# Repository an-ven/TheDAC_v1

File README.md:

# The DAC -The Digital Analog Clock

The primary goal of this project was to design and build a clock, without a single line of code running on the clock hardware. To do this, the time keeping circuit (the digital part) was implemented by hard-wiring together classic 74-series logic chips. The time display was implemented using three analog meters driven by three adjustable current sources (the analog part) controlled by the timekeeping circuit.

As an additional constraint, the circuit was built using only trough hole components (a welcome change of pace, since lately I mostly make circuits with surface mount components)

# Theory of operation

In general the circuit can be presented as follows (for full circuit schematic, refer to [circuit documentation](Documentation/TheDAC_v1.pdf)):

## Crystal oscillator and clock divider

Every clock needs a stable frequency source. In this case, it is based around a common 32,768kHz watch crystal (Y1) and the oscillator section of the 74HC4060 integrated circuit (U3). The chosen oscillator frequency is a power of two (`2^15 = 32768`) which can conveniently be divided down to 1Hz using binary counters.

The oscillator output of 74HC4060 is then internally connected to the first stage clock input of its 14-stage binary ripple counter section. Each counter stage is basically a T-type flip-flop that inverts (toggles) its output state when a falling edge is detected on its clock input. Effectively each stage divides its clock signal frequency by 2. Counter stages are wired in series, where each stage feeds the clock input of the next stage.

Given a 14 stage counter, its input clock frequency will be divided by `2^14 = 16384` on the output of its last (14th) stage. With the oscillator frequency 32,768kHz, the last counter stage will output a 2Hz signal which then gets sent to the seconds counter circuit. In this circuit, the 12th stage output (8Hz signal) is also used by the time setting user interface circuit. 

## Seconds, minutes and hours counters

Hours, minutes and seconds counters are each constructed around a 74HC4024 7-stage binary ripple counter

Looking at the seconds counter (U6), its clock input is driven by a 2Hz signal from the oscillator circuit, which gets divided to 1Hz by the counters first stage and output (Q0) to a test point and a LED (D4). Conveniently this 1Hz signal is also internally wired to the remaining 6 subsequent counter stages with their outputs (Q1 to Q6) representing the seconds count in parallel binary format.

When the seconds counter gets to 60 (or `111100` in binary), the counter should immediately (asynchronously) resets back to 0. This condition is detected by feeding the 4 most significant outputs (Q3 to Q6) in to one of 74HC21 4-input AND gates (U7B) which when all four inputs are high generates a high signal, which can then be used as a reset signal for the second counter and a clock pulse for the minutes counter.

The seconds counter reset signal gets combined with the user interface stop signal by a logic OR function implemented using two NOR gates (U5D and U5C). The clock pulse for the minutes counter is combined with the user interface increment seconds signal and inverted by a NOR gate (U5A).

Moving on to the minutes counter (U8), the circuit functions very similarly to the seconds counter circuit, with differences being that the first counter stage isn't needed for clock division and is directly used as the minutes count least significant bit (LSB) and the minutes counter reset signal is connected directly to the output of the 4-input AND gate (U7A). The last counter stage is simply ignored.

The hours counter follows much the same operating principles with the difference being, that it needs to reset when reaching 24 (`11000` in binary). This function is done by wiring the two most significant hour count bits (outputs Q3 and Q4) through a logical AND block (implemented using two NAND gates U4D and U4C) to the counter reset input. The last two counter stages are ignored.

Some basic logic functions such as hours reset logic AND circuit and seconds reset combining OR circuit have been implemented using multiple logic gates. This was done to avoid having to add additional logic chips with exact needed function and then have several unused logic gates in various chips (most classic 74-series basic logic gate chips usually have multiple logic gates per package)

## Digital to analog conversion and current driver circuit

As mentioned previously, seconds (6 bits), minutes (6 bits) and hours (5 bits) counters output their count values in parallel binary format. These outputs are used to drive 3 digital to analog converters (DAC) that are implemented as simple R-2R resistor ladders.

The analog voltage signals from R-2R DACs are then connected to the current driver inputs. A single current driver is implemented using one of four operational amplifier blocks of the LMC6484 Quad Op-Amp IC (U10). Each Op-Amp block amplifies the voltage difference between its two inputs: `V_out = G * (V(+) - V(-))`, where `G` is amplifier gain (usually a very large number). So if the `V(+)` input goes higher than `V(-)` the Op-Amp output `V_out` will also pull higher and vice versa.

The R-2R DAC output signal is fed in to the Op-Amp `V(+)` input, while its output is wired through an analog micro ampere meter in to its `V(-)` and then through a variable resistor to ground, forming a negative feedback loop. In this configuration the Op-Amp will drive its output so that the `V(-)` input voltage (voltage drop across the adjustable resistor) is effectively equal to `V(+)` input voltage.

With counters at their maximum values (59 for seconds and minutes counters and 23 for hours counter) the variable resistors are set so that the current needed to cause voltage drops across the adjustable resistor equal to ADC output voltage is equal full scale current of analog ampere meters. In this case very sensitive (50uA full range) analog ampere meters have been chosen, so that Op-Amp outputs are powerful enough to drive the needed full scale current without the need for any external amplification stages.  

The unused Op-Amp block has its inputs wired to its power supply rails, so that the output is forced in to a defined state. If the inputs were left floating, tit would be possible for the output to wander around unpredictably, possibly causing interference. In this application this probably wouldn't be an issue, but in a more sensitive circuit this could be critical.

## Time setting user interface

Time setting interface consists of three user inputs: a toggle switch that enables time setting mode and two push buttons used to manually increment minutes and hours counts. Closing the "run/stop" toggle switch (SW1) forces the seconds counter reset input high (stop signal), effectively stopping the counter and holding it at 0, wile also enabling minutes and hours setting push buttons (SW2 and SW3 respectively).

Push button contacts closing together isn't a perfect one time event due to contacts bouncing against each other before settling and completely closing together. The counter chips used in this circuit are more than fast enough to count individual contact bounce events which means one button press can be counted as wildly varying number of button presses. To filter contact bounce out from the push button signal a combination of a low-pass filter and schmitt trigger is used.

Looking at the minute setting circuit, SW2 push button signal (yellow trace) feeds in to the low pass filter consisting of resistor R5 and capacitor C7 (blue trace) which then feeds in to one of two inputs of a 74HC132 schmtt trigger input NAND gate U2D. This filters or "debounces" the raw push button signal. In its idle state the U2D gate is high and for it to go in to its active low state, both inputs need to be high. The second input of U2D is fed by another NAND gate U2C which also idles high.

Gate U2C acts as a valve for the 8Hz signal on one of its inputs, which gets used to automatically increment after a delay period if the button SW2 is kept closed. The time delay circuit consists of resistor R6, capacitor C5 and diode D2. When SW2 is closed, C2 slowly charges trough R6 which after some time charges to a level that triggers the schmitt trigger input, which opens the path for the 8Hz signal to start toggling the U2D gate output. When SW2 is released, capacitor C7 quickly discharges trough diode D2 and resistor R3, resetting the time delay for the next button press.

Finally, because an active high signal is needed to increment the counter, the output of U2D is inverted (purple trace) using another NAND gate U4B that is wired to act as a NOT gate.

The hour setting circuit is identical to the minute setting circuit

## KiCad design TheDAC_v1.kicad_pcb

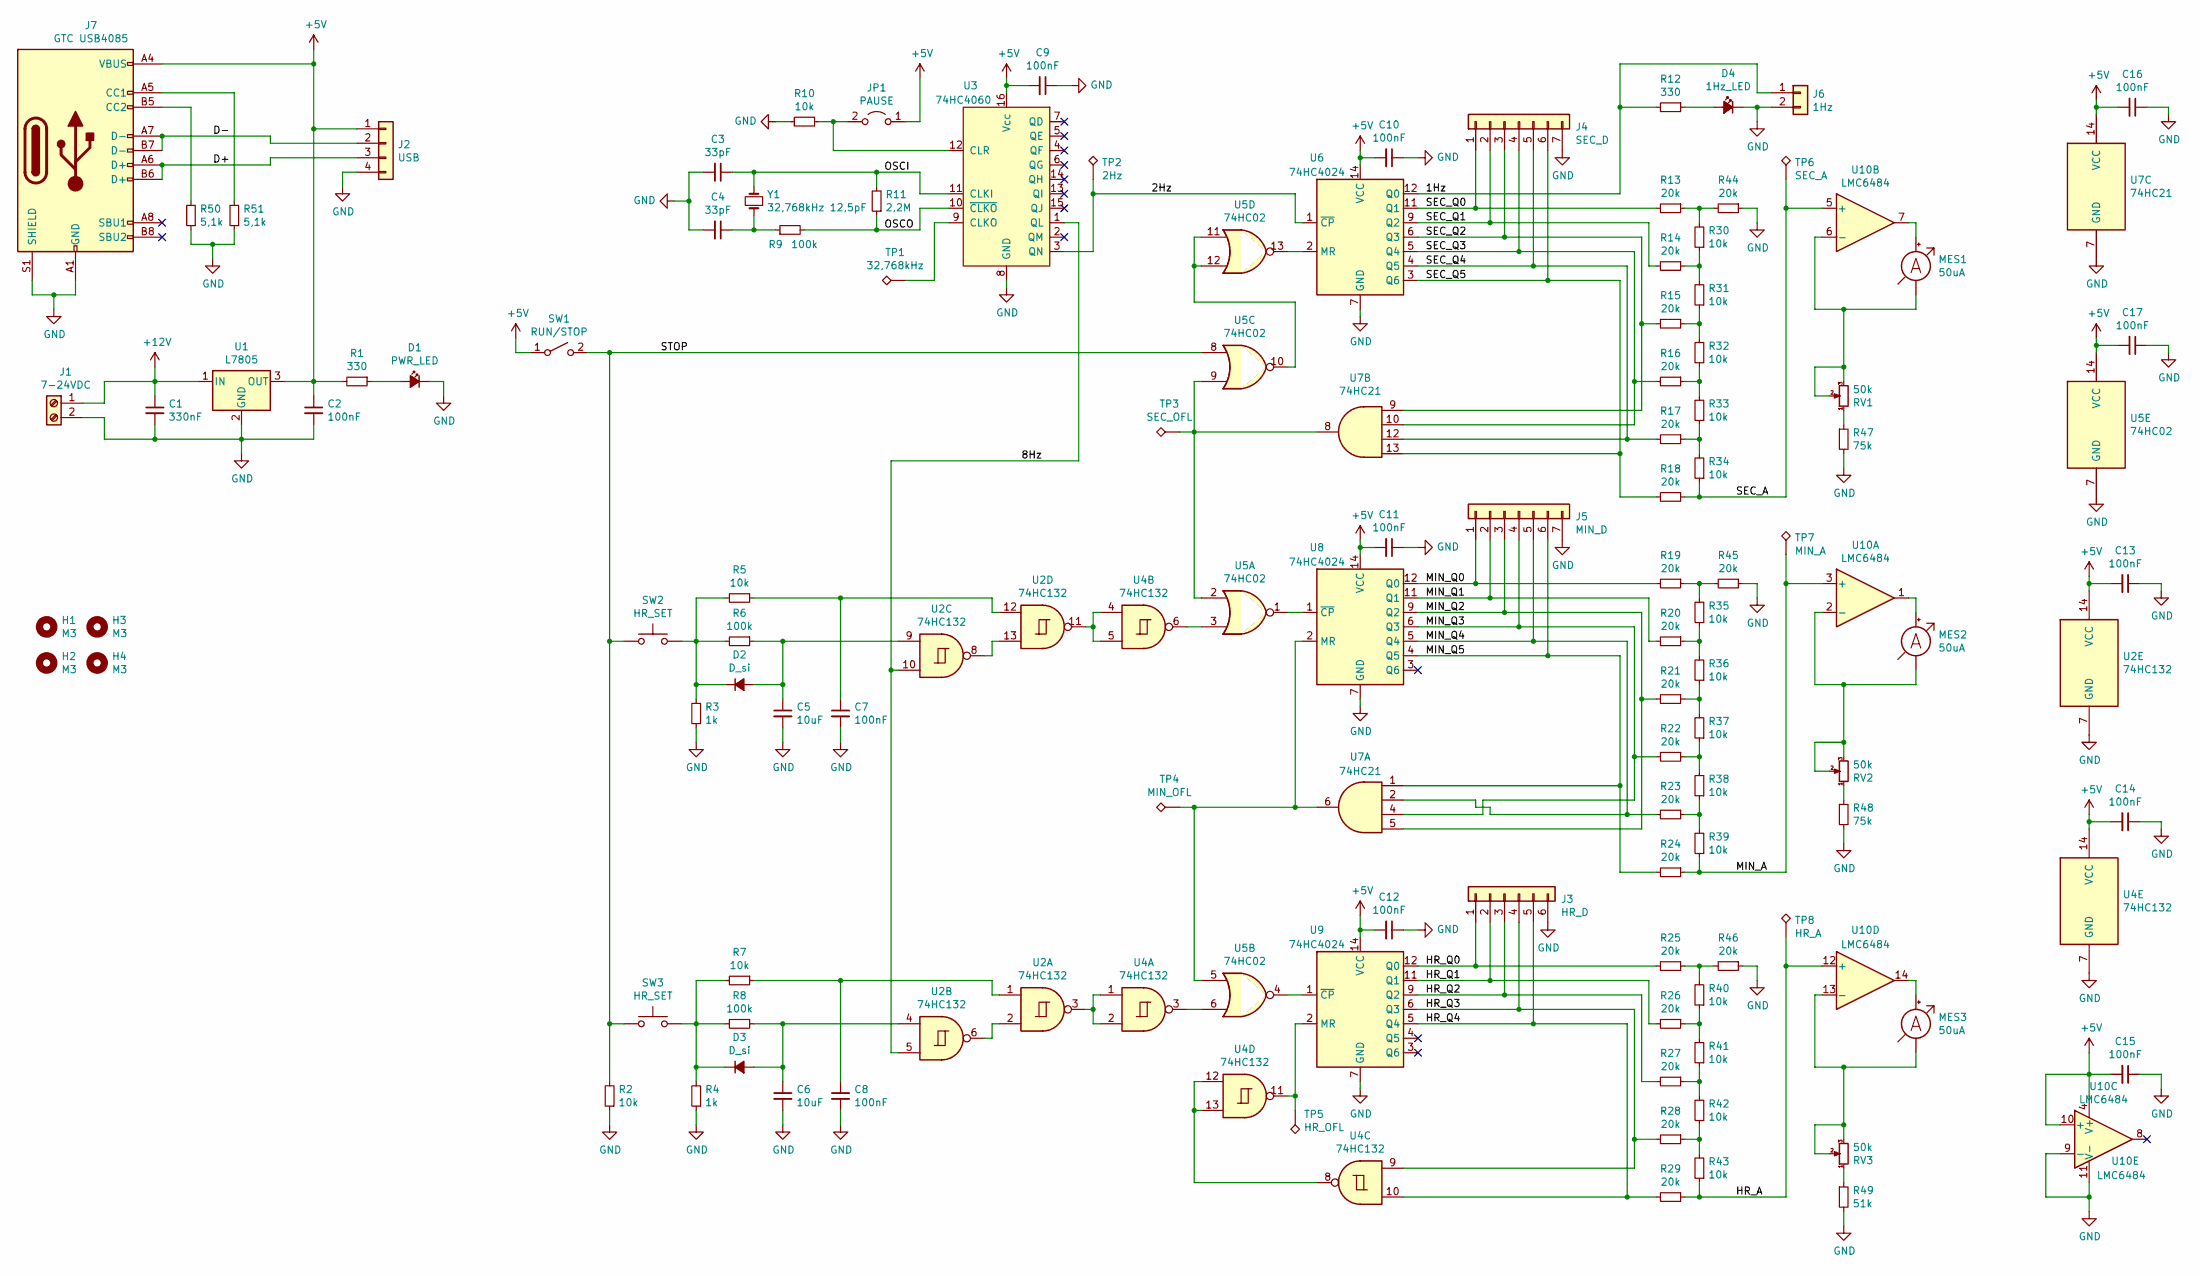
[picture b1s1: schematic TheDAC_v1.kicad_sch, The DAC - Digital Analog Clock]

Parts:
C1: 330nF; C_Disc_D5.1mm_W3.2mm_P5.00mm
C2, C7, C8, C9, C10, C11, C12, C13, C14, C15, C16, C17: 100nF; C_Disc_D4.7mm_W2.5mm_P5.00mm
C3, C4: 33pF; C_Disc_D4.3mm_W1.9mm_P5.00mm
C5, C6: 10uF; C_Disc_D5.1mm_W3.2mm_P5.00mm
D1: PWR_LED; LED_D5.0mm
D2, D3: D_si; D_DO-41_SOD81_P10.16mm_Horizontal
D4: 1Hz_LED; LED_D5.0mm
H1, H2, H3, H4: M3; MountingHole_3.2mm_M3_Pad_Via
J1: 7-24VDC; TerminalBlock_Phoenix_MKDS-1,5-2-5.08_1x02_P5.08mm_Horizont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
J2: USB; PinHeader_1x04_P2.54mm_Vertical
J3: HR_D; PinHeader_1x06_P2.54mm_Vertical
J4: SEC_D; PinHeader_1x07_P2.54mm_Vertical
J5: MIN_D; PinHeader_1x07_P2.54mm_Vertical
J6: 1Hz; PinHeader_1x02_P2.54mm_Vertical
J7: GTC USB4085; USB_C_Receptacle_GCT_USB4085
JP1: PAUSE; PinHeader_1x02_P2.54mm_Vertical
MES1, MES2, MES3: 50uA; TerminalBlock_Phoenix_MKDS-1,5-2-5.08_1x02_P5.08mm_Horizont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
R1, R12: 330; R_Axial_DIN0207_L6.3mm_D2.5mm_P10.16mm_Horizontal
R2, R5, R7, R10, R30, R31, R32, R33, R34, R35, R36, R37, R38, R39, R40, R41, R42, R43: 10k; R_Axial_DIN0207_L6.3mm_D2.5mm_P10.16mm_Horizontal
R3, R4: 1k; R_Axial_DIN0207_L6.3mm_D2.5mm_P10.16mm_Horizontal
R6, R8, R9: 100k; R_Axial_DIN0207_L6.3mm_D2.5mm_P10.16mm_Horizontal
R11: 2,2M; R_Axial_DIN0207_L6.3mm_D2.5mm_P10.16mm_Horizontal
R13, R14, R15, R16, R17, R18, R19, R20, R21, R22, R23, R24, R25, R26, R27, R28, R29, R44, R45, R46: 20k; R_Axial_DIN0207_L6.3mm_D2.5mm_P10.16mm_Horizontal
R47, R48: 75k; R_Axial_DIN0207_L6.3mm_D2.5mm_P10.16mm_Horizontal
R49: 51k; R_Axial_DIN0207_L6.3mm_D2.5mm_P10.16mm_Horizontal
R50, R51: 5,1k; R_Axial_DIN0207_L6.3mm_D2.5mm_P10.16mm_Horizontal
RV1, RV2, RV3: 50k; Potentiometer_Bourns_3296Z_Horizontal
SW1: RUN/STOP; TerminalBlock_Phoenix_MKDS-1,5-2-5.08_1x02_P5.08mm_Horizont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
SW2, SW3: HR_SET; TerminalBlock_Phoenix_MKDS-1,5-2-5.08_1x02_P5.08mm_Horizont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
TP1: 32,768kHz; TestPoint_THTPad_D2.0mm_Drill1.0mm
TP2: 2Hz; TestPoint_THTPad_D2.0mm_Drill1.0mm
TP3: SEC_OFL; TestPoint_THTPad_D2.0mm_Drill1.0mm
TP4: MIN_OFL; TestPoint_THTPad_D2.0mm_Drill1.0mm
TP5: HR_OFL; TestPoint_THTPad_D2.0mm_Drill1.0mm
TP6: SEC_A; TestPoint_THTPad_D2.0mm_Drill1.0mm
TP7: MIN_A; TestPoint_THTPad_D2.0mm_Drill1.0mm
TP8: HR_A; TestPoint_THTPad_D2.0mm_Drill1.0mm
U1: L7805; TO-220F-3_Horizontal_TabDown
U2, U4: 74HC132; DIP-14_W7.62mm_LongPads
U3: 74HC4060; DIP-16_W7.62mm_LongPads
U5: 74HC02; DIP-14_W7.62mm_LongPads
U6, U8, U9: 74HC4024; DIP-14_W7.62mm_LongPads
U7: 74HC21; DIP-14_W7.62mm_LongPads
U10: LMC6484; DIP-14_W7.62mm_LongPads
Y1: 32,768kHz 12,5pF; Crystal_C38-LF_D3.0mm_L8.0mm_Horizontal

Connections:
+5V: C2.1, C9.2, C10.2, C11.2, C12.2, C13.2, C14.2, C15.2, C16.2, C17.2, J2.1, J7.A4 (VBUS), J7.A9 (VBUS), J7.B4 (VBUS), J7.B9 (VBUS), JP1.1 (A), R1.2, SW1.1 (A), U1.3 (OUT), U2.14 (VCC), U3.16 (Vcc), U4.14 (VCC), U5.14 (VCC), U6.14 (VCC), U7.14 (VCC), U8.14 (VCC), U9.14 (VCC), U10.4 (V+), U10.10 (+)
+12V: C1.1, J1.1, U1.1 (IN)
/1Hz: J6.1, R12.2, U6.12 (Q0)
/2Hz: TP2.1, U3.3 (QN), U6.1 (~CP)
/8Hz: U2.5, U2.10, U3.1 (QL)
/D+: J2.3, J7.A6 (D+), J7.B6 (D+)
/D-: J2.2, J7.A7 (D-), J7.B7 (D-)
/HR_A: R29.1, R43.1, TP8.1, U10.12 (+)
/HR_Q0: J3.1, R25.2, U9.12 (Q0)
/HR_Q1: J3.2, R26.2, U9.11 (Q1)
/HR_Q2: J3.3, R27.2, U9.9 (Q2)
/HR_Q3: J3.4, R28.2, U4.9, U9.6 (Q3)
/HR_Q4: J3.5, R29.2, U4.10, U9.5 (Q4)
/MIN_A: R24.1, R39.1, TP7.1, U10.3 (+)
/MIN_Q0: J5.1, R19.2, U8.12 (Q0)
/MIN_Q1: J5.2, R20.2, U8.11 (Q1)
/MIN_Q2: J5.3, R21.2, U7.5, U8.9 (Q2)
/MIN_Q3: J5.4, R22.2, U7.4, U8.6 (Q3)
/MIN_Q4: J5.5, R23.2, U7.2, U8.5 (Q4)
/MIN_Q5: J5.6, R24.2, U7.1, U8.4 (Q5)
/OSCI: C3.1, R11.2, U3.11 (CLKI), Y1.2
/OSCO: R9.2, R11.1, U3.10 (~CLKO)
/SEC_A: R18.1, R34.1, TP6.1, U10.5 (+)
/SEC_Q0: J4.1, R13.2, U6.11 (Q1)
/SEC_Q1: J4.2, R14.2, U6.9 (Q2)
/SEC_Q2: J4.3, R15.2, U6.6 (Q3), U7.9
/SEC_Q3: J4.4, R16.2, U6.5 (Q4), U7.10
/SEC_Q4: J4.5, R17.2, U6.4 (Q5), U7.12
/SEC_Q5: J4.6, R18.2, U6.3 (Q6), U7.13
/STOP: R2.2, SW1.2 (B), SW2.1, SW3.1, U5.8
GND: C1.2, C2.2, C3.2, C4.2, C5.2, C6.2, C7.2, C8.2, C9.1, C10.1, C11.1, C12.1, C13.1, C14.1, C15.1, C16.1, C17.1, D1.1 (K), D4.1 (K), J1.2, J2.4, J3.6, J4.7, J5.7, J6.2, J7.A1 (GND), J7.A12 (GND), J7.B1 (GND), J7.B12 (GND), J7.S1 (SHIELD), R2.1, R3.1, R4.1, R10.2, R44.1, R45.1, R46.1, R47.2, R48.2, R49.2, R50.1, R51.1, U1.2 (GND), U2.7 (GND), U3.8 (GND), U4.7 (GND), U5.7 (GND), U6.7 (GND), U7.7 (GND), U8.7 (GND), U9.7 (GND), U10.9 (-), U10.11 (V-)
unnamed: C4.1, R9.1, Y1.1
unnamed: C5.1, D2.2 (A), R6.1, U2.9
unnamed: C6.1, D3.2 (A), R8.1, U2.4
unnamed: C7.1, R5.1, U2.12
unnamed: C8.1, R7.1, U2.1
unnamed: D1.2 (A), R1.1
unnamed: D2.1 (K), R3.2, R5.2, R6.2, SW2.2
unnamed: D3.1 (K), R4.2, R7.2, R8.2, SW3.2
unnamed: D4.2 (A), R12.1
unnamed: J7.A5 (CC1), R51.2
unnamed: J7.B5 (CC2), R50.2
unnamed: JP1.2 (B), R10.1, U3.12 (CLR)
unnamed: MES1.1 (-), RV1.2, RV1.3, U10.6 (-)
unnamed: MES1.2 (+), U10.7
unnamed: MES2.1 (-), RV2.2, RV2.3, U10.2 (-)
unnamed: MES2.2 (+), U10.1
unnamed: MES3.1 (-), RV3.2, RV3.3, U10.13 (-)
unnamed: MES3.2 (+), U10.14
unnamed: R13.1, R30.2, R44.2
unnamed: R14.1, R30.1, R31.2
unnamed: R15.1, R31.1, R32.2
unnamed: R16.1, R32.1, R33.2
unnamed: R17.1, R33.1, R34.2
unnamed: R19.1, R35.2, R45.2
unnamed: R20.1, R35.1, R36.2
unnamed: R21.1, R36.1, R37.2
unnamed: R22.1, R37.1, R38.2
unnamed: R23.1, R38.1, R39.2
unnamed: R25.1, R40.2, R46.2
unnamed: R26.1, R40.1, R41.2
unnamed: R27.1, R41.1, R42.2
unnamed: R28.1, R42.1, R43.2
unnamed: R47.1, RV1.1
unnamed: R48.1, RV2.1
unnamed: R49.1, RV3.1
unnamed: TP1.1, U3.9 (CLKO)
unnamed: TP3.1, U5.2, U5.9, U7.8
unnamed: TP4.1, U5.5, U7.6, U8.2 (MR)
unnamed: TP5.1, U4.11, U9.2 (MR)
unnamed: U2.2, U2.6
unnamed: U2.3, U4.1, U4.2
unnamed: U2.11, U4.4, U4.5
unnamed: U2.8, U2.13
unnamed: U4.3, U5.6
unnamed: U4.6, U5.3
unnamed: U4.8, U4.12, U4.13
unnamed: U5.1, U8.1 (~CP)
unnamed: U5.4, U9.1 (~CP)
unnamed: U5.10, U5.11, U5.12
unnamed: U5.13, U6.2 (MR)

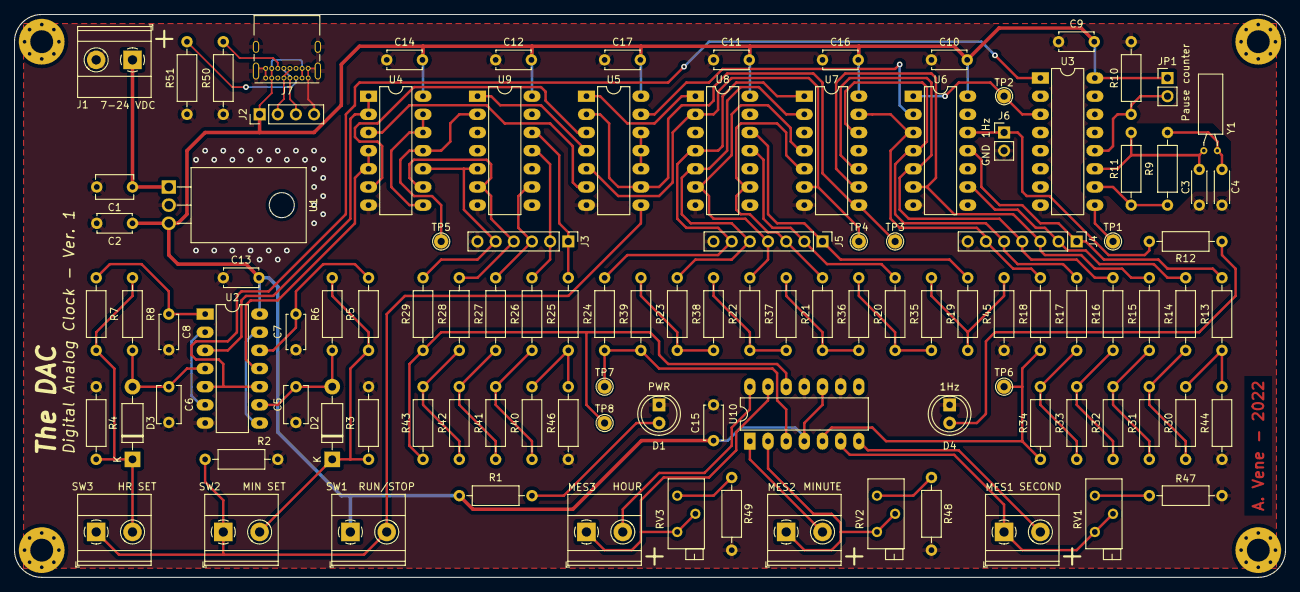
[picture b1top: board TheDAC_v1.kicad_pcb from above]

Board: 2 copper layers, 177.8 x 78.7 mm, 112 parts (0 on the bottom side), 81 nets.

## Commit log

2023-01-12 Add licese, couple of minor fixes in README
